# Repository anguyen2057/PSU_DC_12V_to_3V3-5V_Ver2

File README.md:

# PSU_DC_12V_to_3V3-5V_Ver2
A compact switching power supply unit (PSU) that converts a 12V input to regulated 3.3V and 5V outputs.

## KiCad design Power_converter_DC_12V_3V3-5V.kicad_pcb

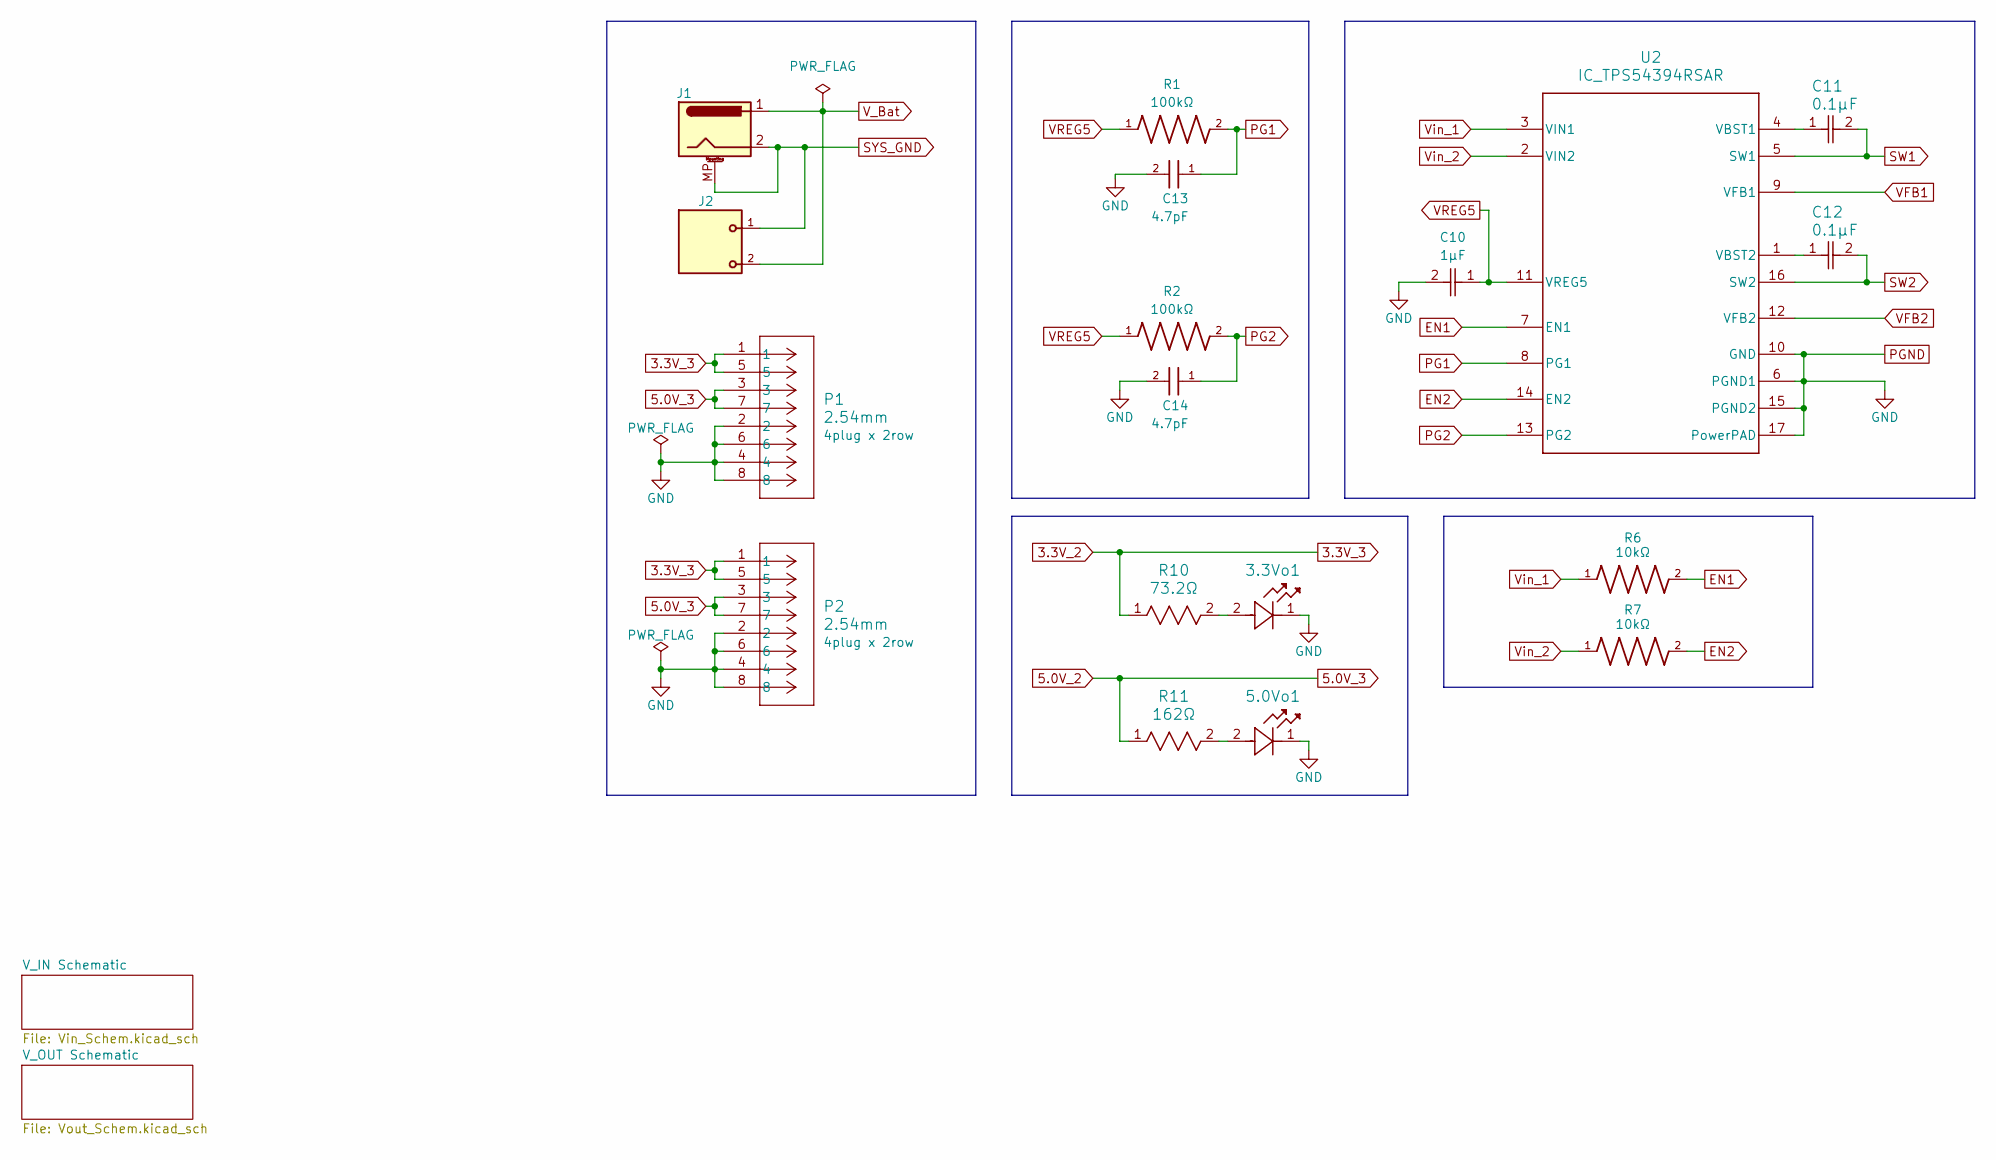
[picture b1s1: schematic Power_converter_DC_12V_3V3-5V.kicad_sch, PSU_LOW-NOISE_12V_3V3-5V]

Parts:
3.3Vo1, 5.0Vo1: LED_1.9V_Forward_SML-E12DWT86; LED_SMLD12_ROM
C10: 1µF; CAPC1608X90N; DigiKey_Part_Number 445-5146-2-ND
C11, C12: 0.1µF; CAP_CL10_SAM
C13, C14: 4.7pF; WCAP-CSGP_0603_R
J1: Barrel_Jack_MountingPin; BarrelJack_Wuerth_6941xx301002
J2: 691412120002B; PART-NUMBER 691412120002B
P1, P2: 2.54mm; CONN_PEC04_AA_SUL
R1, R2: 100kΩ; RES_ERJP06D1003V; PARTREV 3/1/2020
R6, R7: 10kΩ; RESC3015X65N
R10: 73.2Ω; RC1206N_YAG
R11: 162Ω; RC1206N_YAG
U2: IC_TPS54394RSAR; RSA0016B-IPC_A

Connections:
3.3V_2: P1.1, P1.5, P2.1, P2.5, R10.1; also elsewhere on the board
5.0V_2: P1.3, P1.7, P2.3, P2.7, R11.1; also elsewhere on the board
EN1: R6.2, U2.7 (EN1)
EN2: R7.2, U2.14 (EN2)
unnamed: 3.3Vo1.2, R10.2
unnamed: 5.0Vo1.2, R11.2
unnamed: C11.1, U2.4 (VBST1)
unnamed: C12.1, U2.1 (VBST2)
PG1: C13.1, R1.2, U2.8 (PG1)
PG2: C14.1, R2.2, U2.13 (PG2)
PGND: 3.3Vo1.1, 5.0Vo1.1, C10.2, C13.2, C14.2, P1.2, P1.4, P1.6, P1.8, P2.2, P2.4, P2.6, P2.8, U2.6 (PGND1), U2.10 (GND), U2.15 (PGND2), U2.17 (PowerPAD); also elsewhere on the board
SW1: C11.2, U2.5 (SW1); also elsewhere on the board
SW2: C12.2, U2.16 (SW2); also elsewhere on the board
SYS_GND: J1.2, J1.3, J1.MP (MountPin), J2.1; also elsewhere on the board
VFB1: U2.9 (VFB1); also elsewhere on the board
VFB2: U2.12 (VFB2); also elsewhere on the board
VREG5: C10.1, R1.1, R2.1, U2.11 (VREG5)
V_Bat: J1.1, J2.2; also elsewhere on the board
Vin_1: R6.1, U2.3 (VIN1); also elsewhere on the board
Vin_2: R7.1, U2.2 (VIN2); also elsewhere on the board

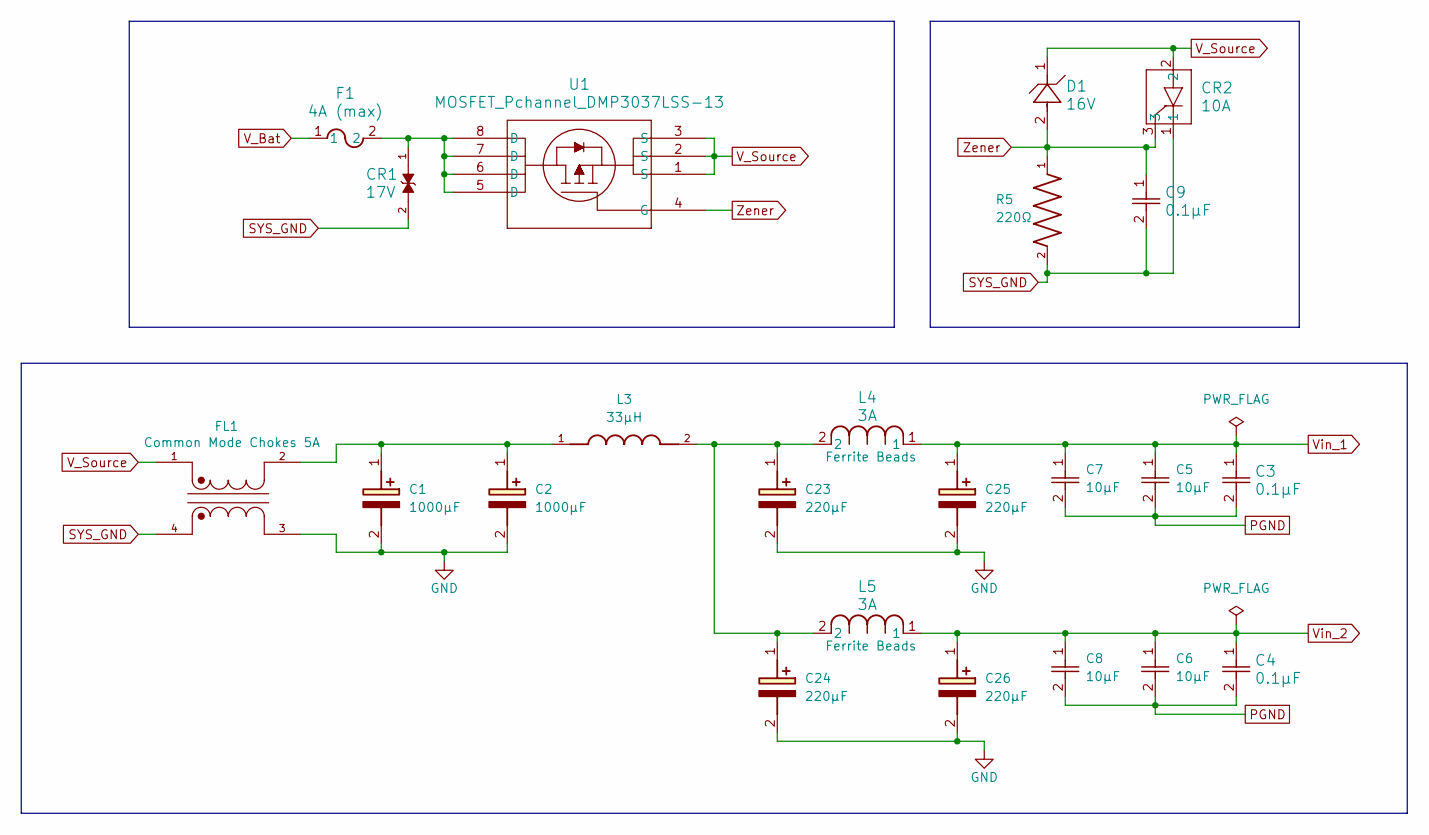
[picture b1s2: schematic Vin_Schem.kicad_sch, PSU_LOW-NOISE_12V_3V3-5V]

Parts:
C1, C2: 1000µF; CAPPRD500W65D1000H1600; Mouser Part Number 80-A750MV108M1EAAE14
C3, C4, C9: 0.1µF; CAP_CL10_SAM
C5, C6, C7, C8: 10µF; CAPC3216X140N
C23, C24, C25, C26: 220µF; CAPPRD350W65D800H1300; Mouser Part Number A750KS227M1EEAE015
CR1: 17V; SMASeries_LTF
CR2: 10A; DPAK_6p73x6p22-2p286_STM
D1: 16V; SOD323F_DIO
F1: 4A (max); FUSE_31.8221_SCH
FL1: Common Mode Chokes 5A; FIL_ACMP-5025-251-T; PARTREV B
L3: 33µH; IND_ETQP4M330KVC; PARTREV 1-Feb-20
L4, L5: 3A; IND_1608_TDK
R5: 220Ω; RESC3116X65N
U1: MOSFET_Pchannel_DMP3037LSS-13; SO8_DIO

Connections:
unnamed: C1.1 (+), C2.1 (+), FL1.2, L3.1
unnamed: C23.1 (+), C24.1 (+), L3.2, L4.2, L5.2
unnamed: CR1.1, F1.2, U1.5 (D), U1.6 (D), U1.7 (D), U1.8 (D)
PGND: C1.2 (-), C2.2 (-), C3.2, C4.2, C5.2, C6.2, C7.2, C8.2, C23.2 (-), C24.2 (-), C25.2 (-), C26.2 (-), FL1.3; also elsewhere on the board
SYS_GND: C9.2, CR1.2, CR2.1, FL1.4, R5.2; also elsewhere on the board
V_Bat: F1.1; also elsewhere on the board
V_Source: CR2.2, D1.1, FL1.1, U1.1 (S), U1.2 (S), U1.3 (S)
Vin_1: C3.1, C5.1, C7.1, C25.1 (+), L4.1; also elsewhere on the board
Vin_2: C4.1, C6.1, C8.1, C26.1 (+), L5.1; also elsewhere on the board
Zener: C9.1, CR2.3, D1.2, R5.1, U1.4 (G)

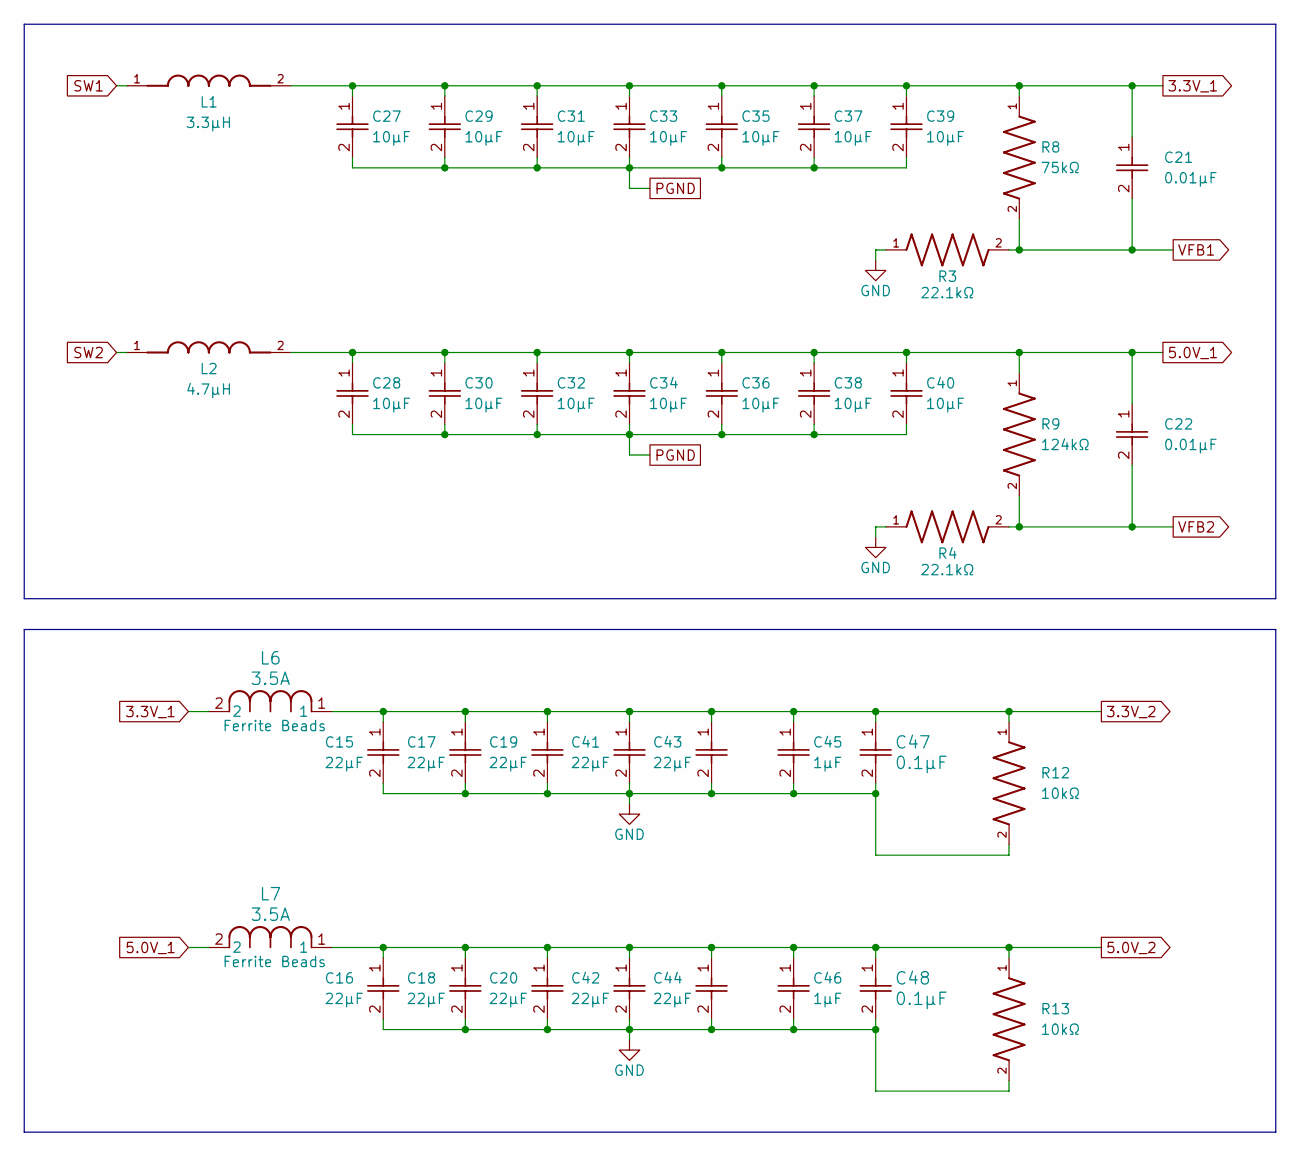
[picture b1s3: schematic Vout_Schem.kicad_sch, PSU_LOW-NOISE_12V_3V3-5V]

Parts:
C15, C16, C17, C18, C19, C20, C41, C42, C43, C44: 22µF; CAPC3216X180N
C21, C22: 0.01µF; CAPC1608X90N
C27, C28, C29, C30, C31, C32, C33, C34, C35, C36, C37, C38, C39, C40: 10µF; CAPC3216X140N
C45, C46: 1µF; CAPC1608X90N; DigiKey_Part_Number 445-5146-2-ND
C47, C48: 0.1µF; CAP_CL10_SAM
L1: 3.3µH; IND_VLS6045EX-3R3N; PARTREV N/A
L2: 4.7µH; IND_VLS6045EX-4R7M; PARTREV N/A
L6, L7: 3.5A; IND_1608_TDK
R3, R4: 22.1kΩ; RESC2012X60N
R8: 75kΩ; RESC2012X60N
R9: 124kΩ; RES_ERJ-PB6B1243V; PARTREV 3/1/2020
R12, R13: 10kΩ; RESC3015X65N

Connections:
3.3V_1: C21.1, C27.1, C29.1, C31.1, C33.1, C35.1, C37.1, C39.1, L1.2, L6.2, R8.1
3.3V_2: C15.1, C17.1, C19.1, C41.1, C43.1, C45.1, C47.1, L6.1, R12.1; also elsewhere on the board
5.0V_1: C22.1, C28.1, C30.1, C32.1, C34.1, C36.1, C38.1, C40.1, L2.2, L7.2, R9.1
5.0V_2: C16.1, C18.1, C20.1, C42.1, C44.1, C46.1, C48.1, L7.1, R13.1; also elsewhere on the board
PGND: C15.2, C16.2, C17.2, C18.2, C19.2, C20.2, C27.2, C28.2, C29.2, C30.2, C31.2, C32.2, C33.2, C34.2, C35.2, C36.2, C37.2, C38.2, C39.2, C40.2, C41.2, C42.2, C43.2, C44.2, C45.2, C46.2, C47.2, C48.2, R3.1, R4.1, R12.2, R13.2; also elsewhere on the board
SW1: L1.1; also elsewhere on the board
SW2: L2.1; also elsewhere on the board
VFB1: C21.2, R3.2, R8.2; also elsewhere on the board
VFB2: C22.2, R4.2, R9.2; also elsewhere on the board

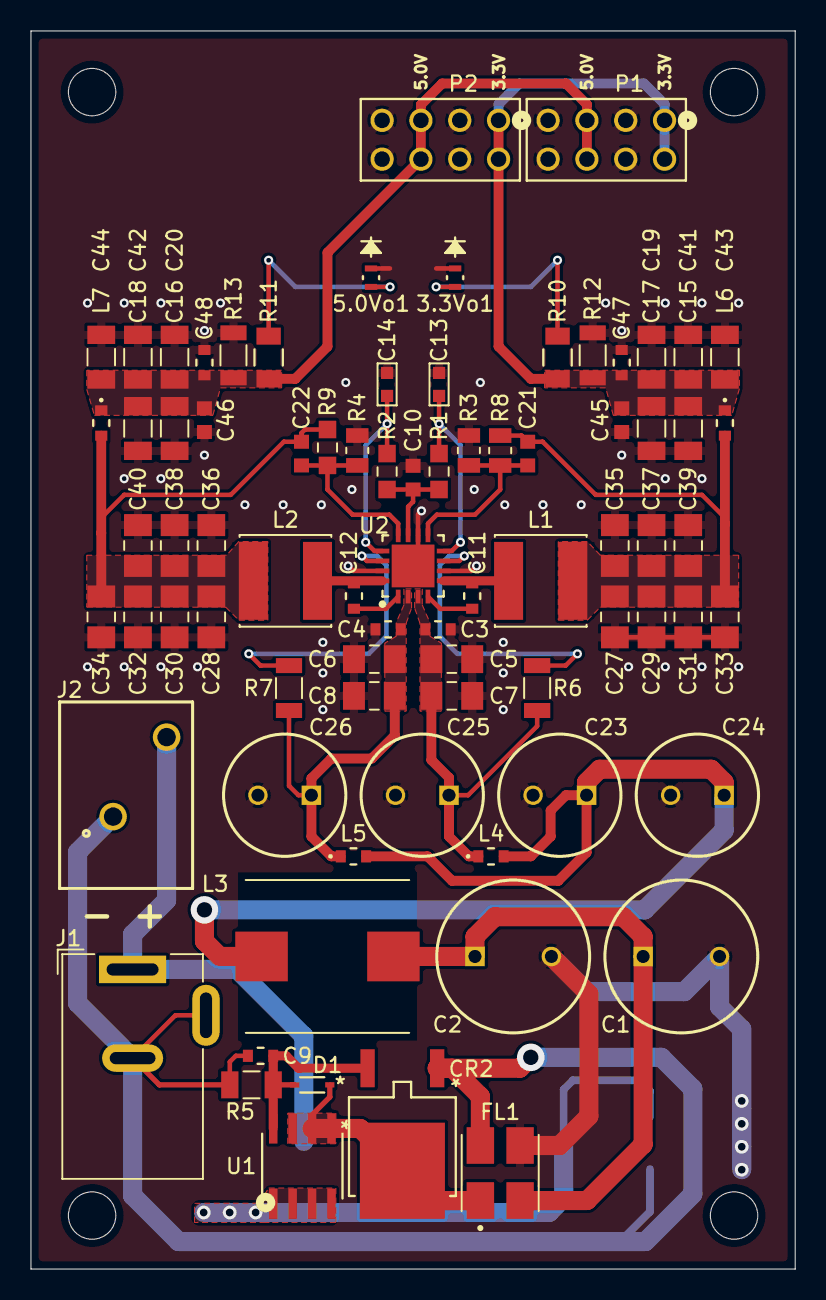
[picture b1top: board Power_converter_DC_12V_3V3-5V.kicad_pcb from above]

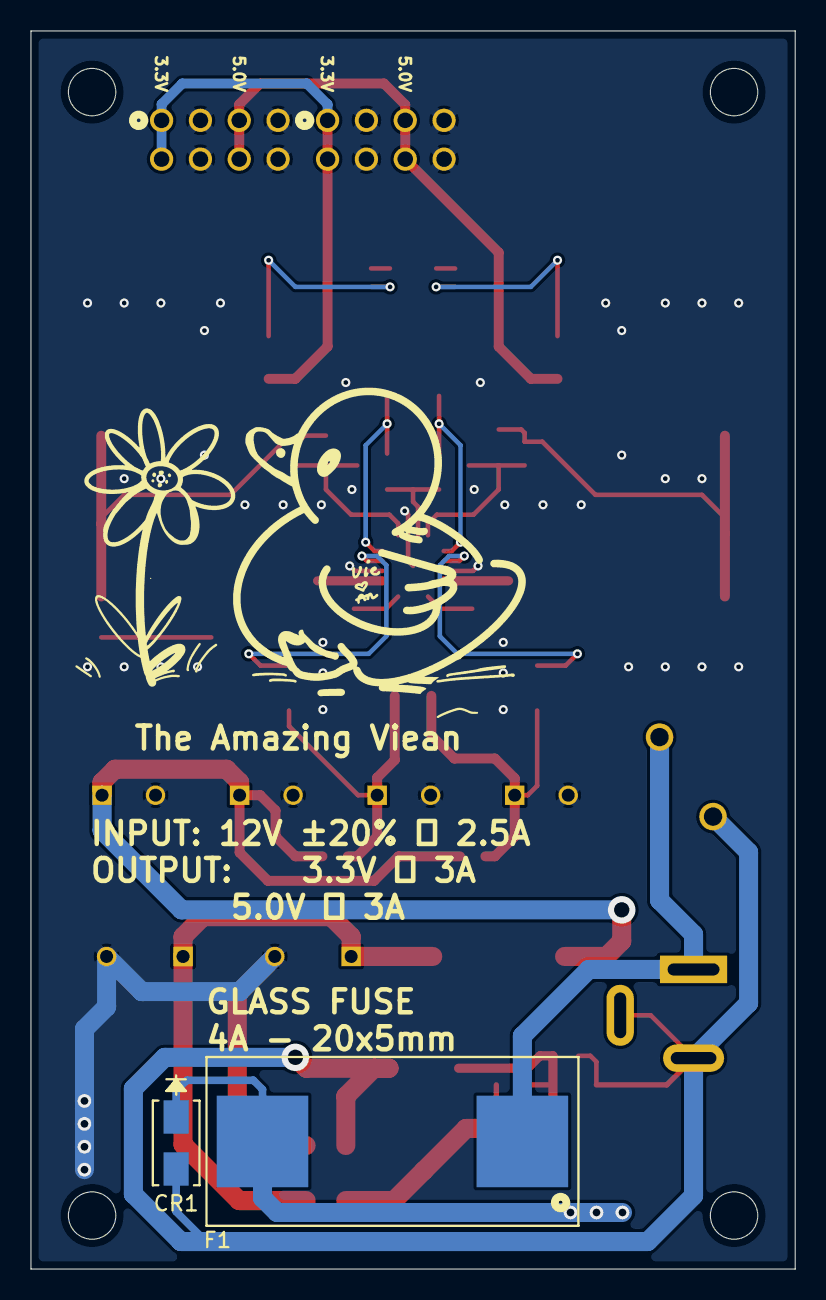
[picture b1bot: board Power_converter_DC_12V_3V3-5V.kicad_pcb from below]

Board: 2 copper layers, 50.0 x 81.0 mm, 82 parts (3 on the bottom side), 27 nets.

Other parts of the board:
The Amazing Viean: LOGO; Logo_Drawing

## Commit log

2025-02-19 Uploading the Files
2025-02-21 PSU Schematic
2025-02-21 3D View of the PCB
    Top and Bottom views of the PCB
